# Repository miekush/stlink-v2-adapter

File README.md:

# STLINK_V2_Adapter
An adapter board for using 10-pin ARM debug cables and 4-pin SWD cables with the STLINK V2

# Project Description

After I was unable to find a simple adapter board for using 10-pin ARM cables and 4-pin SWD cables with the ST LINK, I decided to design my own!

# SWD Connector

# Tag-Connect

# BOM

| Component | Supplier | Part Number |
| --- | --- | --- |
| `JTAG 20P` | Sullins | SFH11-PBPC-D10-ST-BK |
| `ARM 10P` | Sullins | SBH11-PBPC-D05-ST-BK |
| `SWD 4P` | Generic | 2.54MM RA Strip Header |

# License

MKE supports the open source hardware community by sharing hardware design files freely on GitHub!

Please support MKE by purchasing products on [Tindie](https://www.tindie.com/stores/miekush/)!

Designed by Mike Kushnerik for MKEngineering

Licensed under [Creative Commons Attribution-ShareAlike CC BY-SA 3.0](http://creativecommons.org/licenses/by-sa/3.0/)

All text above must be included in any redistribution!

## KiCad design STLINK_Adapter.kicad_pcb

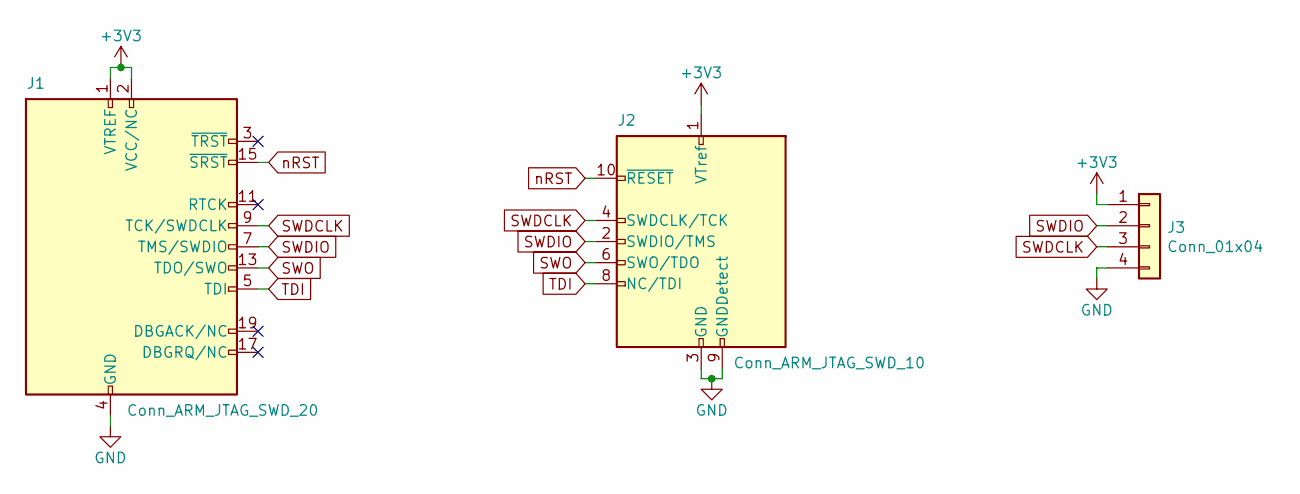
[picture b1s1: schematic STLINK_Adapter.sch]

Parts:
J1: Conn_ARM_JTAG_SWD_20; PinSocket_2x10_P2.54mm_Vertical
J2: Conn_ARM_JTAG_SWD_10; Multicomp_MC9A12-1034_2x05_P2.54mm_Vertical
J3: Conn_01x04; PinHeader_1x04_P2.54mm_Vertical

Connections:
+3V3: J1.1 (VTREF), J1.2 (VCC/NC), J2.1 (VTref), J3.1
GND: J1.4 (GND), J1.6 (GND), J1.8 (GND), J1.10 (GND), J1.12 (GND), J1.14 (GND), J1.16 (GND), J1.18 (GND), J1.20 (GND), J2.3 (GND), J2.5 (GND), J2.9 (GNDDetect), J3.4
SWDCLK: J1.9 (TCK/SWDCLK), J2.4 (SWDCLK/TCK), J3.3
SWDIO: J1.7 (TMS/SWDIO), J2.2 (SWDIO/TMS), J3.2
SWO: J1.13 (TDO/SWO), J2.6 (SWO/TDO)
TDI: J1.5 (TDI), J2.8 (NC/TDI)
nRST: J1.15 (~SRST~), J2.10 (~RESET~)

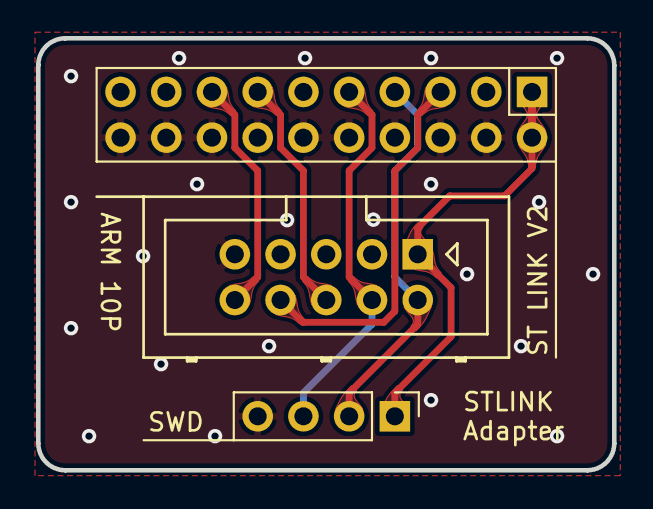
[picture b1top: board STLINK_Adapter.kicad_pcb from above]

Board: 2 copper layers, 32.0 x 24.0 mm, 3 parts (1 on the bottom side), 7 nets.

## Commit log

2021-05-28 Initial Upload
